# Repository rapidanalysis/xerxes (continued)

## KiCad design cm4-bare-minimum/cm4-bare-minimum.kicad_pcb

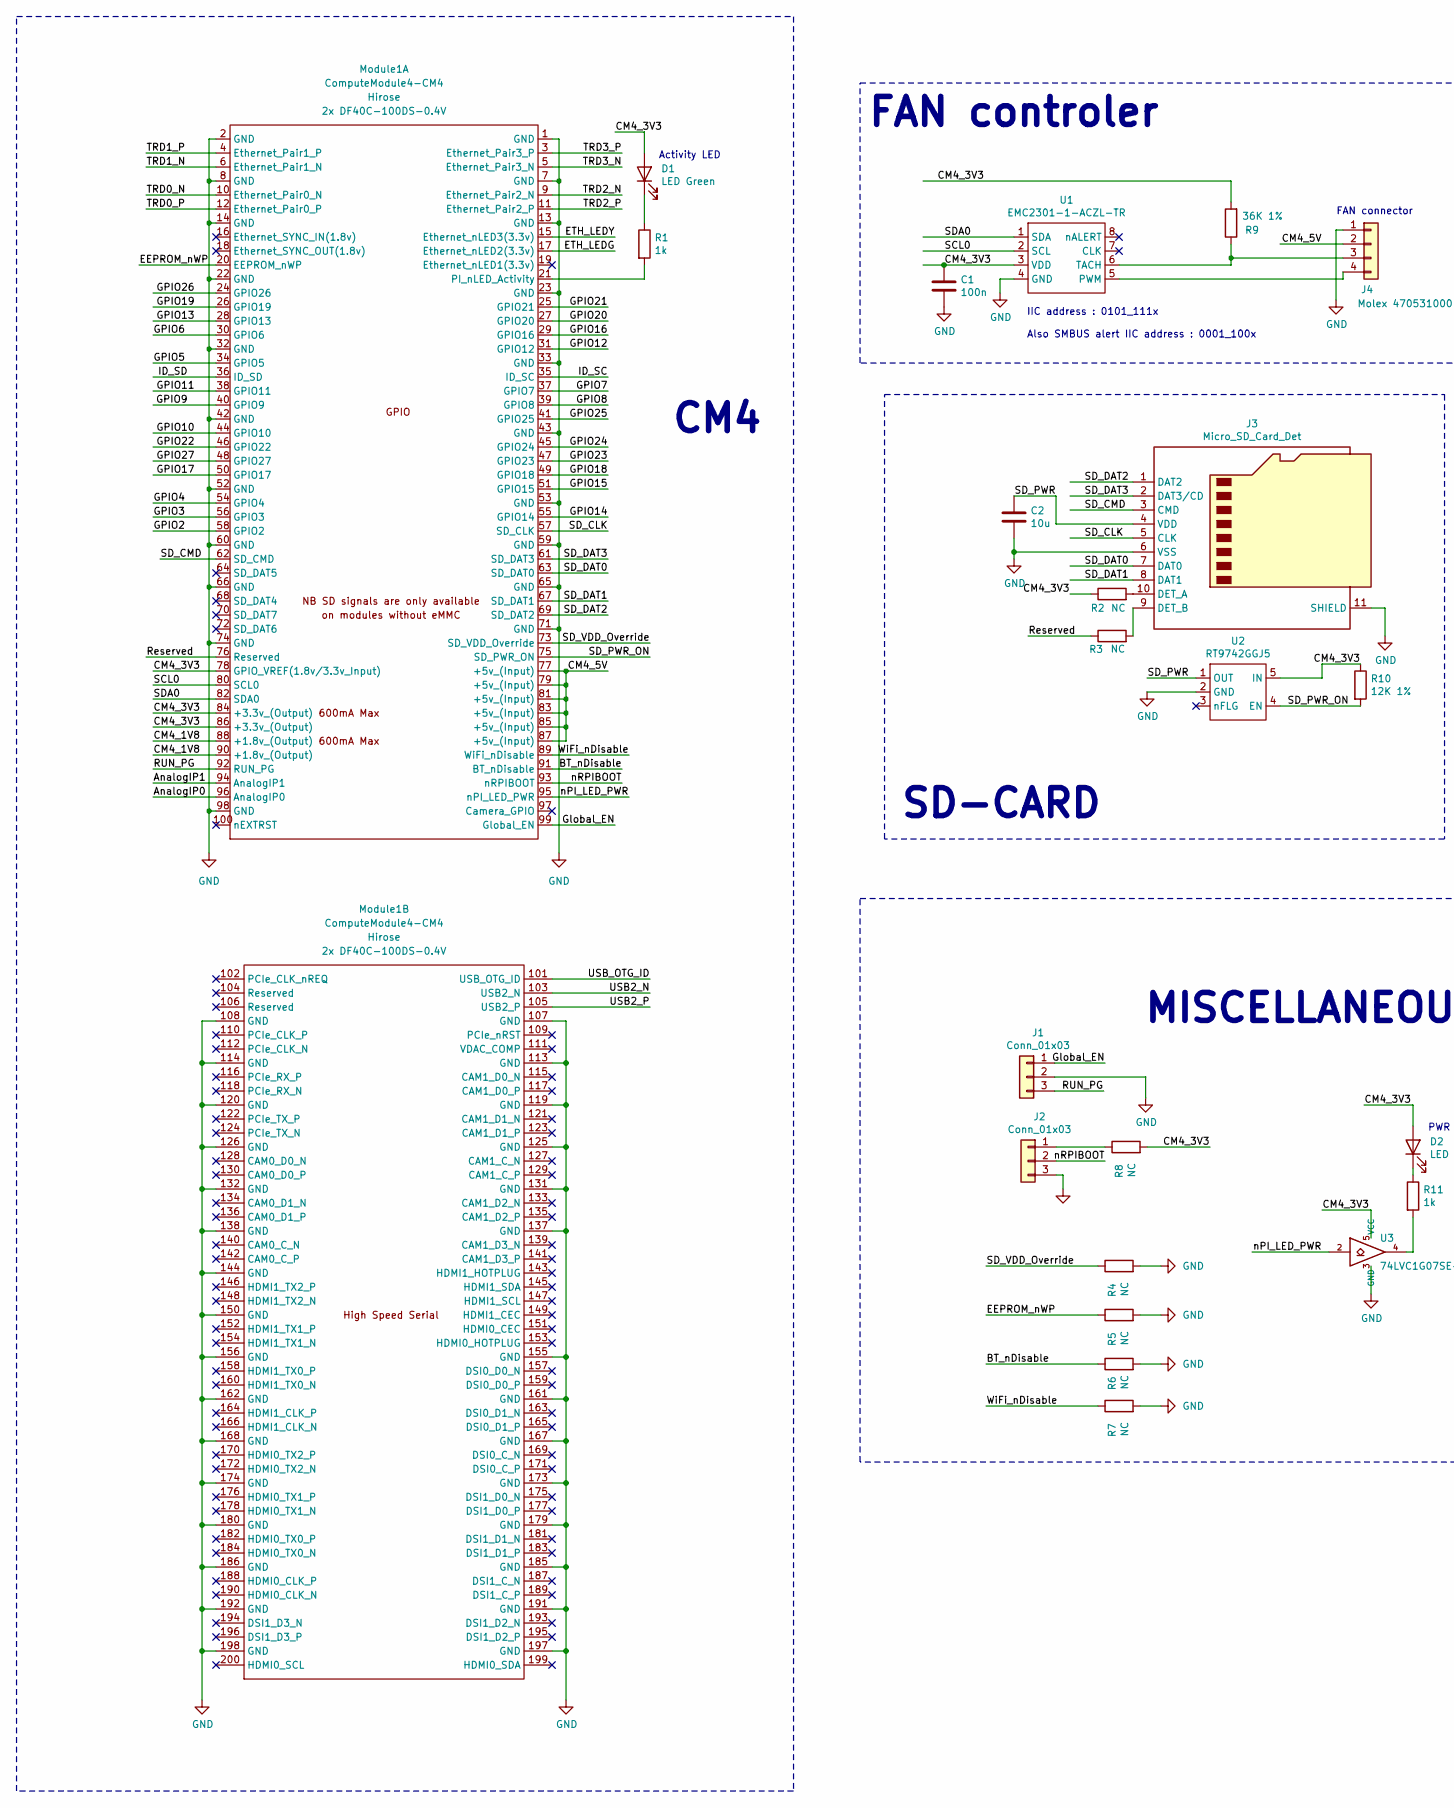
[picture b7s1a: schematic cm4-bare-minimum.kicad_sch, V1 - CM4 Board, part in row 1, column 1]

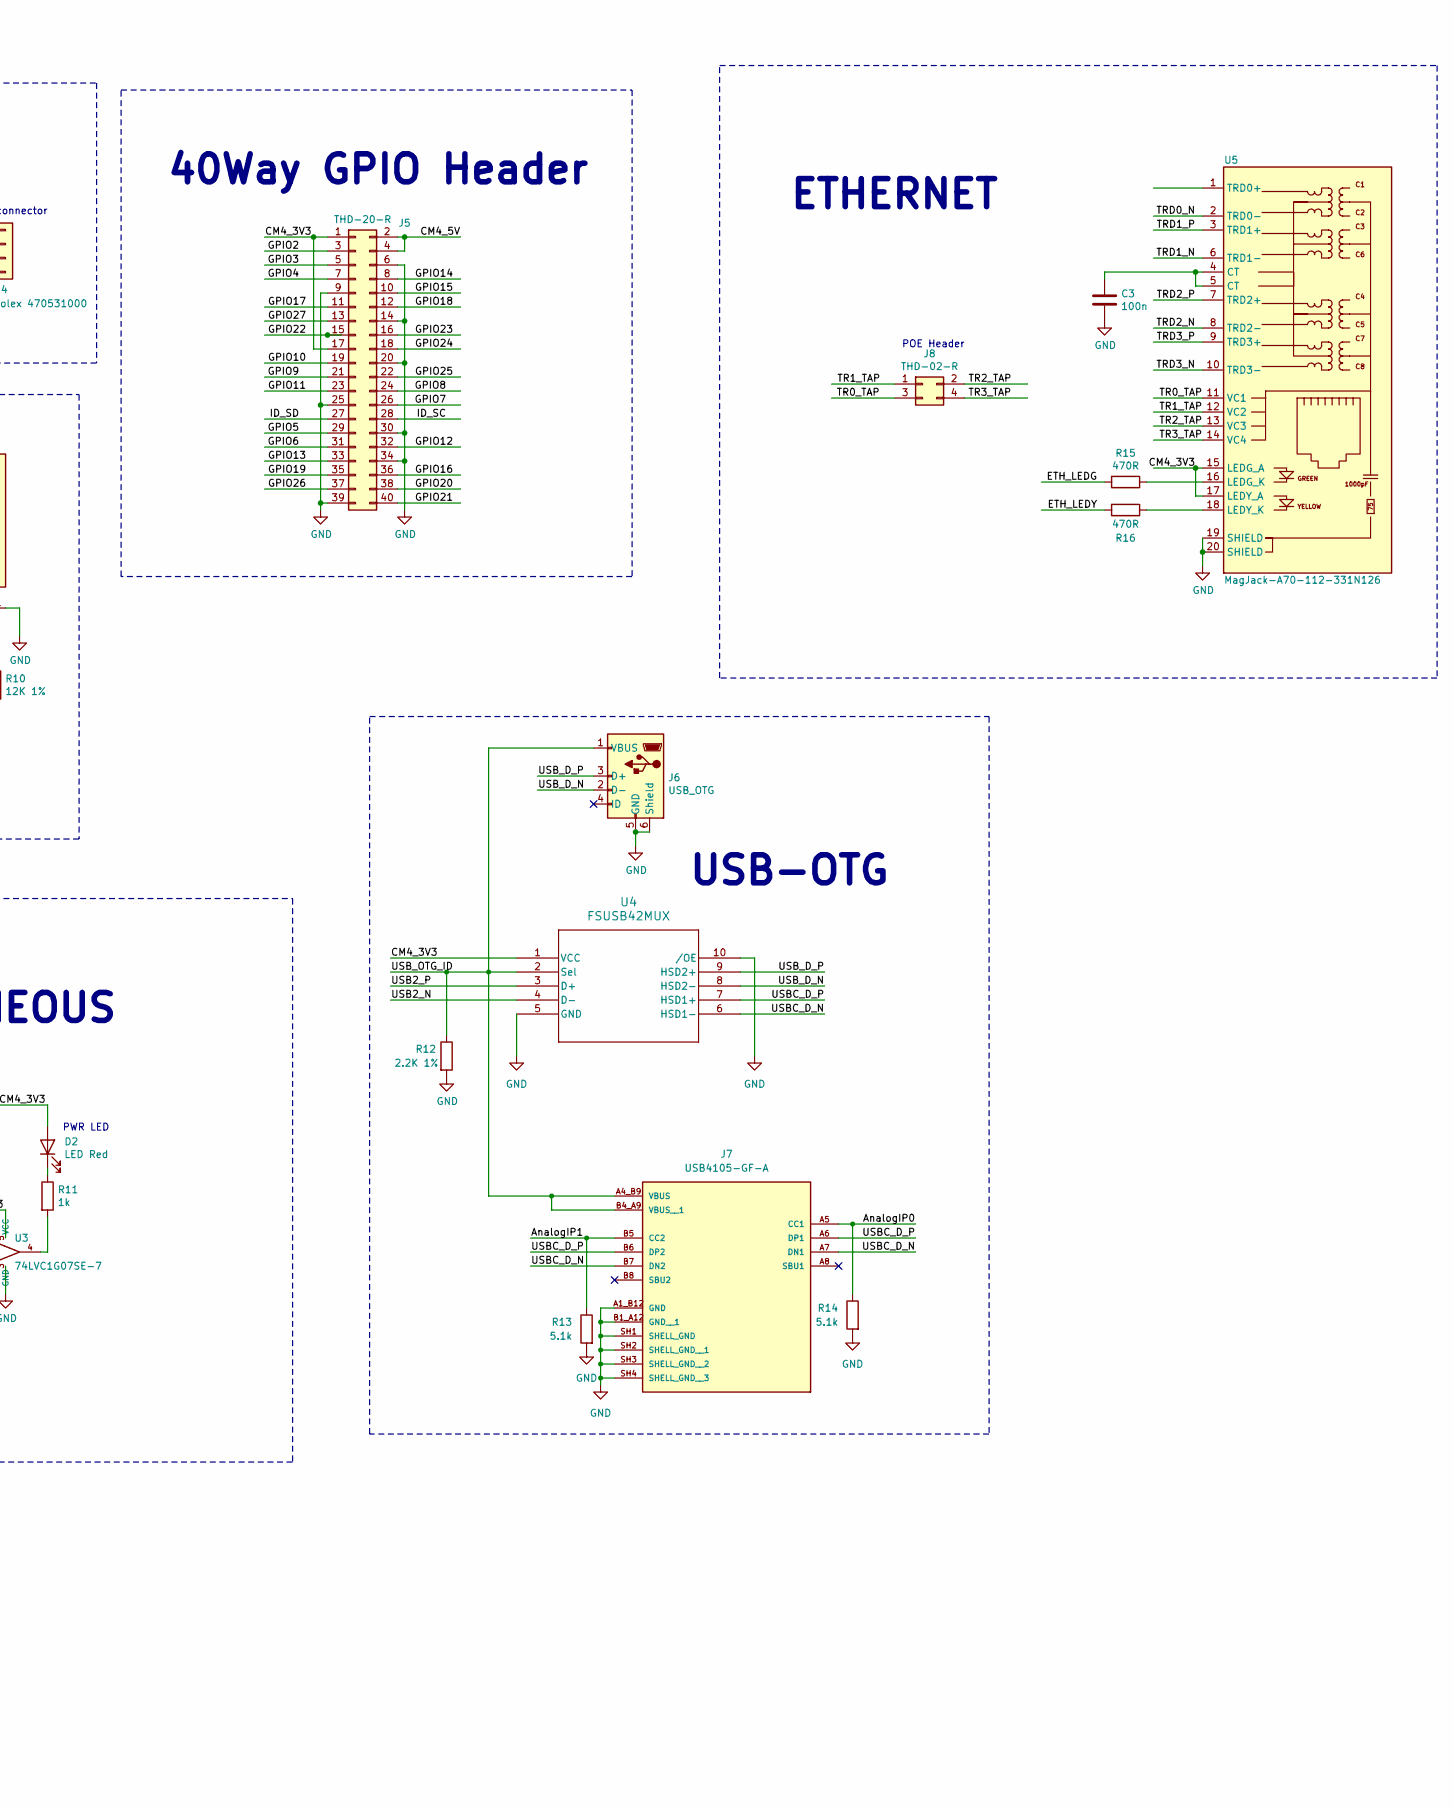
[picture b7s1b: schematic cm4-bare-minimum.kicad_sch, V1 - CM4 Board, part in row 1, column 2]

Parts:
C1, C3: 100n; C_0402_1005Metric; Part Description 0.1uF 10% 16V Ceramic Capacitor X7R 040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
C2: 10u; C_0805_2012Metric; Part Description 10uF 10% 10V Ceramic Capacitor X7R 0805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
D1: LED Green; LED_0603_1608Metric; Part Description Green 572nm LED Indication - Discrete 2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
D2: LED Red; LED_0603_1608Metric; Part Description Red 620nm LED Indication - Discrete 2.2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
J1, J2: Conn_01x03; PinHeader_1x03_P2.54mm_Vertical; Part Description 3pin 0.1" connector
J3: Micro_SD_Card_Det; SDCARD_MOLEX_503398-1892; Part Description 9 (8 + 1) Position Card Connector micro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
J4: Molex 470531000; FanPinHeader_1x04_P2.54mm_Vertical; Part Description Connector Header Through Hole 4 positio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
J5: THD-20-R; PinHeader_2x20_P2.54mm_Vertical; Part Description PinHeader_2x20_P2.54mm_Vertical
J6: USB_OTG; USB_Micro-B_EDAC_UCON00686; Part Description USB - micro B USB 2.0 Receptacle Connec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
J7: USB4105-GF-A; GCT_USB4105-GF-A; PARTREV B4
J8: THD-02-R; PinHeader_2x02_P2.54mm_Vertical; Part Description PinHeader_2x02_P2.54mm_Vertical
Module1: ComputeModule4-CM4; Raspberry-Pi-4-Compute-Module
R1, R11: 1k; R_0402_1005Metric; Part Description Resistor 1K M1005 1% 63mW
R2, R3: NC; R_0402_1005Metric; Part Description Resistor 1K M1005 1% 63mW
R4, R5, R6, R7, R8: NC; R_0402_1005Metric; Part Description Resistor 2.2K M1005 1% 63mW
R9: 36K 1%; R_0402_1005Metric; Part Description Resistor 36K M1005 1% 63mW
R10: 12K 1%; R_0402_1005Metric; Part Description Resistor 12K M1005 1% 63mW
R12: 2.2K 1%; R_0402_1005Metric; Part Description Resistor 2.2K M1005 1% 63mW
R13, R14: 5.1k; R_0402_1005Metric
R15, R16: 470R; R_0402_1005Metric; Part Description Resistor 470R M1005 1% 63mW
U1: EMC2301-1-ACZL-TR; MSOP-8_3x3mm_P0.65mm; Part Description Motor Driver PWM 8-MSOP
U2: RT9742GGJ5; SOT-23-5; Part Description Power Switch/Driver 1:1 N-Channel 1A TS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
U3: 74LVC1G07SE-7; SOT-353_SC-70-5; Part Description Buffer, Non-Inverting 1 Element 1 Bit p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
U4: FSUSB42MUX; MSOP10_3X3_ONS
U5: MagJack-A70-112-331N126; TRJG0926HENL; Part Description Gigabit Ethernet Magjack

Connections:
/AnalogIP0: J7.A5 (CC1), Module1.96 (AnalogIP0), R14.1
/AnalogIP1: J7.B5 (CC2), Module1.94 (AnalogIP1), R13.1
/BT_nDisable: Module1.91 (BT_nDisable), R6.1
/CM4_1V8: Module1.88 (+1.8v_(Output)), Module1.90 (+1.8v_(Output))
/CM4_3V3: C1.1, D1.2 (A), D2.2 (A), J5.1, J5.17, Module1.78 (GPIO_VREF(1.8v/3.3v_Input)), Module1.84 (+3.3v_(Output)), Module1.86 (+3.3v_(Output)), R2.1, R8.2, R9.2, R10.1, U1.3 (VDD), U2.5 (IN), U3.5 (VCC), U4.1 (VCC), U5.15 (LEDG_A), U5.17 (LEDY_A)
/CM4_5V: J4.2, J5.2, J5.4, Module1.77 (+5v_(Input)), Module1.79 (+5v_(Input)), Module1.81 (+5v_(Input)), Module1.83 (+5v_(Input)), Module1.85 (+5v_(Input)), Module1.87 (+5v_(Input))
/EEPROM_nWP: Module1.20 (EEPROM_nWP), R5.1
/ETH_LEDG: Module1.17 (Ethernet_nLED2(3.3v)), R15.2
/ETH_LEDY: Module1.15 (Ethernet_nLED3(3.3v)), R16.2
/GPIO2: J5.3, Module1.58 (GPIO2)
/GPIO3: J5.5, Module1.56 (GPIO3)
/GPIO4: J5.7, Module1.54 (GPIO4)
/GPIO5: J5.29, Module1.34 (GPIO5)
/GPIO6: J5.31, Module1.30 (GPIO6)
/GPIO7: J5.26, Module1.37 (GPIO7)
/GPIO8: J5.24, Module1.39 (GPIO8)
/GPIO9: J5.21, Module1.40 (GPIO9)
/GPIO10: J5.19, Module1.44 (GPIO10)
/GPIO11: J5.23, Module1.38 (GPIO11)
/GPIO12: J5.32, Module1.31 (GPIO12)
/GPIO13: J5.33, Module1.28 (GPIO13)
/GPIO14: J5.8, Module1.55 (GPIO14)
/GPIO15: J5.10, Module1.51 (GPIO15)
/GPIO16: J5.36, Module1.29 (GPIO16)
/GPIO17: J5.11, Module1.50 (GPIO17)
/GPIO18: J5.12, Module1.49 (GPIO18)
/GPIO19: J5.35, Module1.26 (GPIO19)
/GPIO20: J5.38, Module1.27 (GPIO20)
/GPIO21: J5.40, Module1.25 (GPIO21)
/GPIO22: J5.15, Module1.46 (GPIO22)
/GPIO23: J5.16, Module1.47 (GPIO23)
/GPIO24: J5.18, Module1.45 (GPIO24)
/GPIO25: J5.22, Module1.41 (GPIO25)
/GPIO26: J5.37, Module1.24 (GPIO26)
/GPIO27: J5.13, Module1.48 (GPIO27)
/Global_EN: J1.1, Module1.99 (Global_EN)
/ID_SC: J5.28, Module1.35 (ID_SC)
/ID_SD: J5.27, Module1.36 (ID_SD)
/RUN_PG: J1.3, Module1.92 (RUN_PG)
/Reserved: Module1.76 (Reserved), R3.1
/SCL0: Module1.80 (SCL0), U1.2 (SCL)
/SDA0: Module1.82 (SDA0), U1.1 (SDA)
/SD_CLK: J3.5 (CLK), Module1.57 (SD_CLK)
/SD_CMD: J3.3 (CMD), Module1.62 (SD_CMD)
/SD_DAT0: J3.7 (DAT0), Module1.63 (SD_DAT0)
/SD_DAT1: J3.8 (DAT1), Module1.67 (SD_DAT1)
/SD_DAT2: J3.1 (DAT2), Module1.69 (SD_DAT2)
/SD_DAT3: J3.2 (DAT3/CD), Module1.61 (SD_DAT3)
/SD_PWR: C2.1, J3.4 (VDD), U2.1 (OUT)
/SD_PWR_ON: Module1.75 (SD_PWR_ON), R10.2, U2.4 (EN)
/SD_VDD_Override: Module1.73 (SD_VDD_Override), R4.1
/TR0_TAP: J8.3, U5.11 (VC1)
/TR1_TAP: J8.1, U5.12 (VC2)
/TR2_TAP: J8.2, U5.13 (VC3)
/TR3_TAP: J8.4, U5.14 (VC4)
/TRD0_N: Module1.10 (Ethernet_Pair0_N), U5.2 (TRD0-)
/TRD0_P: Module1.12 (Ethernet_Pair0_P)
/TRD1_N: Module1.6 (Ethernet_Pair1_N), U5.6 (TRD1-)
/TRD1_P: Module1.4 (Ethernet_Pair1_P), U5.3 (TRD1+)
/TRD2_N: Module1.9 (Ethernet_Pair2_N), U5.8 (TRD2-)
/TRD2_P: Module1.11 (Ethernet_Pair2_P), U5.7 (TRD2+)
/TRD3_N: Module1.5 (Ethernet_Pair3_N), U5.10 (TRD3-)
/TRD3_P: Module1.3 (Ethernet_Pair3_P), U5.9 (TRD3+)
/USB2_N: Module1.103 (USB2_N), U4.4 (D-)
/USB2_P: Module1.105 (USB2_P), U4.3 (D+)
/USBC_D_N: J7.A7 (DN1), J7.B7 (DN2), U4.6 (HSD1-)
/USBC_D_P: J7.A6 (DP1), J7.B6 (DP2), U4.7 (HSD1+)
/USB_D_N: J6.2 (D-), U4.8 (HSD2-)
/USB_D_P: J6.3 (D+), U4.9 (HSD2+)
/USB_OTG_ID: J6.1 (VBUS), J7.A4_B9 (VBUS), J7.B4_A9 (VBUS__1), Module1.101 (USB_OTG_ID), R12.1, U4.2 (Sel)
/WiFi_nDisable: Module1.89 (WiFi_nDisable), R7.1
/nPI_LED_PWR: Module1.95 (nPI_LED_PWR), U3.2
/nRPIBOOT: J2.2, Module1.93 (nRPIBOOT)
GND: C1.2, C2.2, C3.2, J1.2, J2.3, J3.6 (VSS), J3.11 (SHIELD), J4.1, J5.6, J5.9, J5.14, J5.20, J5.25, J5.30, J5.34, J5.39, J6.5 (GND), J6.6 (Shield), J7.A1_B12 (GND), J7.B1_A12 (GND__1), J7.SH1 (SHELL_GND), J7.SH2 (SHELL_GND__1), J7.SH3 (SHELL_GND__2), J7.SH4 (SHELL_GND__3), Module1.1 (GND), Module1.2 (GND), Module1.7 (GND), Module1.8 (GND), Module1.13 (GND), Module1.14 (GND), Module1.22 (GND), Module1.23 (GND), Module1.32 (GND), Module1.33 (GND), Module1.42 (GND), Module1.43 (GND), Module1.52 (GND), Module1.53 (GND), Module1.59 (GND), Module1.60 (GND), Module1.65 (GND), Module1.66 (GND), Module1.71 (GND), Module1.74 (GND), Module1.98 (GND), Module1.107 (GND), Module1.108 (GND), Module1.113 (GND), Module1.114 (GND), Module1.119 (GND), Module1.120 (GND), Module1.125 (GND), Module1.126 (GND), Module1.131 (GND), Module1.132 (GND), Module1.137 (GND), Module1.138 (GND), Module1.144 (GND), Module1.150 (GND), Module1.155 (GND), Module1.156 (GND), Module1.161 (GND), Module1.162 (GND), Module1.167 (GND), Module1.168 (GND), Module1.173 (GND), Module1.174 (GND), Module1.179 (GND), Module1.180 (GND), Module1.185 (GND), Module1.186 (GND), Module1.191 (GND), Module1.192 (GND), Module1.197 (GND), Module1.198 (GND), R4.2, R5.2, R6.2, R7.2, R12.2, R13.2, R14.2, U1.4 (GND), U2.2 (GND), U3.3 (GND), U4.5 (GND), U4.10 (/OE), U5.19 (SHIELD), U5.20 (SHIELD)
unnamed: C3.1, U5.4 (CT), U5.5 (CT)
unnamed: D1.1 (K), R1.1
unnamed: D2.1 (K), R11.1
unnamed: J2.1, R8.1
unnamed: J3.10 (DET_A), R2.2
unnamed: J3.9 (DET_B), R3.2
unnamed: J4.3, R9.1, U1.6 (TACH)
unnamed: J4.4, U1.5 (PWM)
unnamed: Module1.21 (PI_nLED_Activity), R1.2
unnamed: R11.2, U3.4
unnamed: R15.1, U5.16 (LEDG_K)
unnamed: R16.1, U5.18 (LEDY_K)

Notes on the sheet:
FAN controler
40Way GPIO Header
IIC address : 0101_111x
FAN connector
PWR LED
Activity LED
POE Header
Also SMBUS alert IIC address : 0001_100x
MISCELLANEOUS
USB-OTG
ETHERNET
CM4
SD-CARD

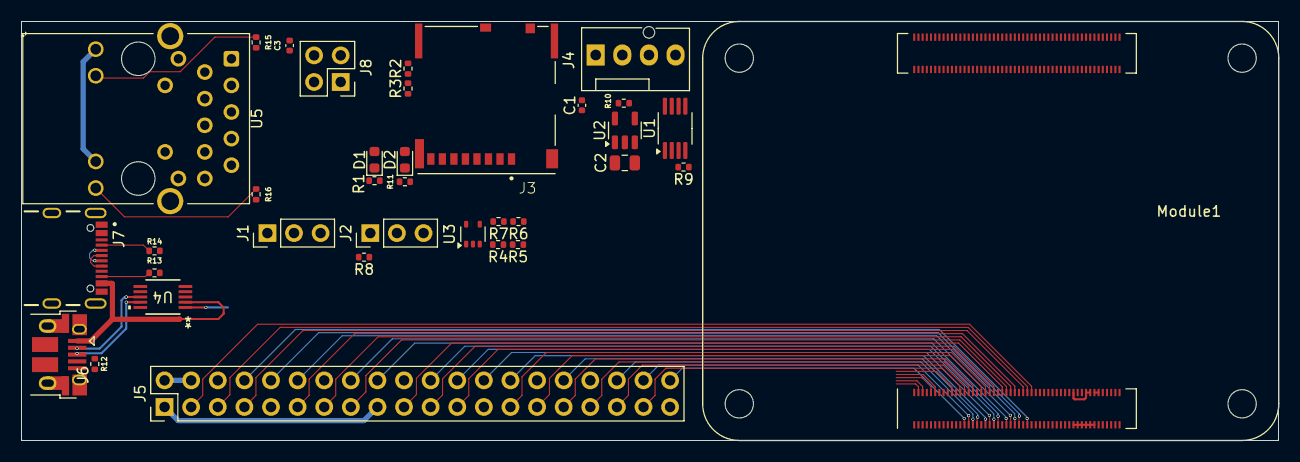
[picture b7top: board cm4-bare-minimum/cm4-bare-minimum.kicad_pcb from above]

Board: 2 copper layers, 120.0 x 40.0 mm, 35 parts (0 on the bottom side), 85 nets.

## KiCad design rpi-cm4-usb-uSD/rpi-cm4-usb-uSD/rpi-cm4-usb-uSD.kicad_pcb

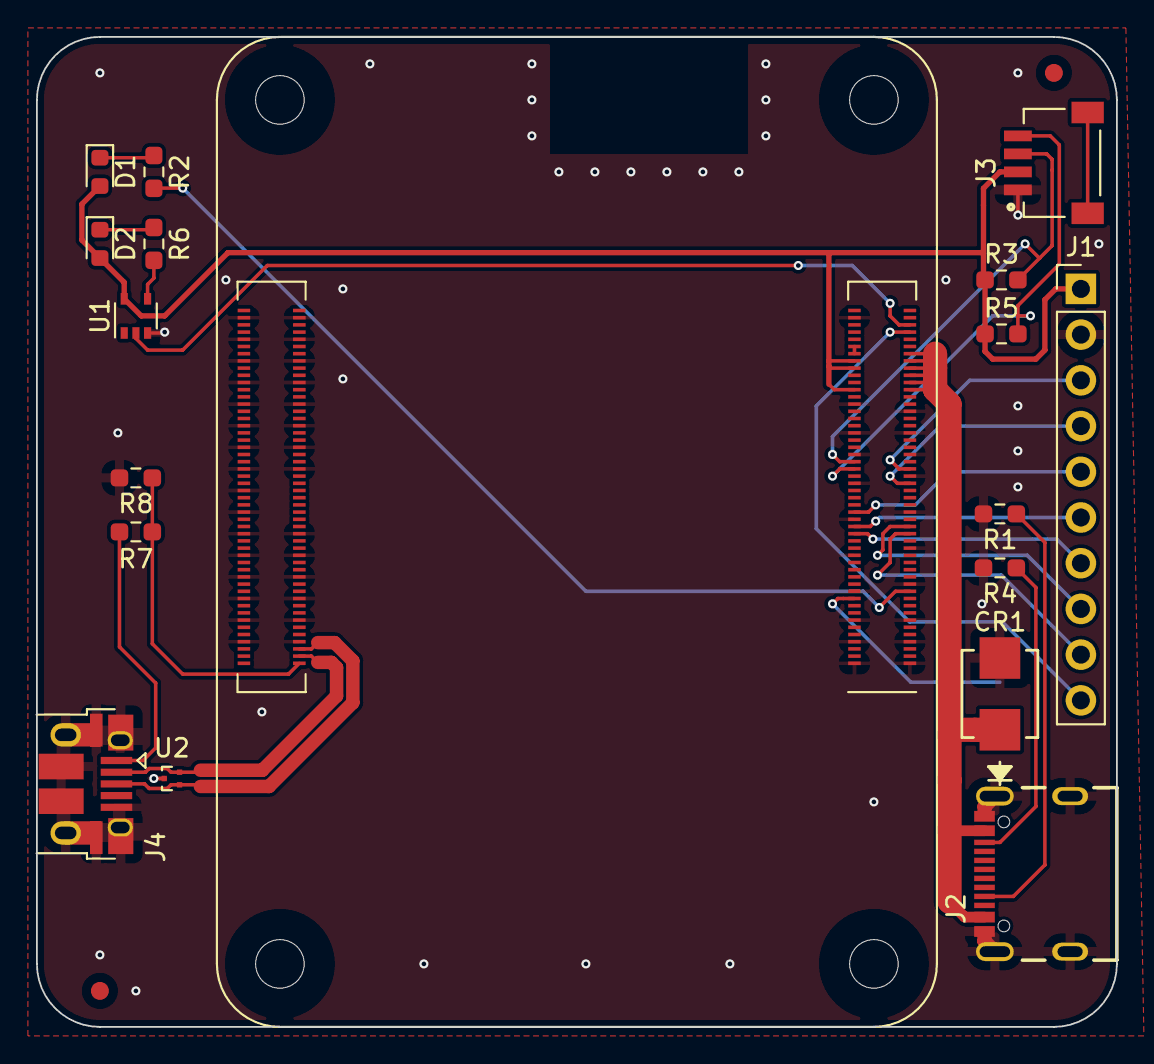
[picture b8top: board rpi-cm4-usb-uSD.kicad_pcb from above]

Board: 2 copper layers, 60.0 x 55.0 mm, 19 parts (1 on the bottom side), 27 nets.

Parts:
CR1: SMBJ5.0A-TR
D1: LED Green; LED_0603_1608Metric
D2: LED Red; LED_0603_1608Metric
J1: DNP; PinHeader_1x10_P2.54mm_Vertical
J2: USB4105-GF-A; GCT_USB4105-GF-A
J3: SM04B-SRSS-TB(LF)(SN); JST_SM04B-SRSS-TB(LF)(SN)
J4: USB_OTG; USB_Micro-B_EDAC_UCON00686
JP1: SolderJumper_2_Open; SolderJumper-2_P1.3mm_Open_RoundedPad1.0x1.5mm
Module1: ComputeModule4-CM4; Raspberry-Pi-4-Compute-Module
R1, R4: 5.1k; R_0603_1608Metric_Pad0.98x0.95mm_HandSolder
R2, R6: 1k; R_0603_1608Metric_Pad0.98x0.95mm_HandSolder
R3, R5: DNP; R_0603_1608Metric_Pad0.98x0.95mm_HandSolder
R7, R8: 2.2K 1%; R_0603_1608Metric_Pad0.98x0.95mm_HandSolder
U1: 74LVC1G07SE-7; SOT-353_SC-70-5
U2: TPD2EUSB30; Texas_DRT-3

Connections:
+1.8V: Module1.88 (+1.8v_(Output)), Module1.90 (+1.8v_(Output))
+3.3V: D1.2 (A), D2.2 (A), J1.1, J3.2, Module1.78 (GPIO_VREF(1.8v/3.3v_Input)), Module1.84 (+3.3v_(Output)), Module1.86 (+3.3v_(Output)), R3.1, R5.1, U1.5 (VCC)
+5V: CR1.1, J2.A4/B9 (VBUS), J2.B4/A9 (VBUS), Module1.77 (+5v_(Input)), Module1.79 (+5v_(Input)), Module1.81 (+5v_(Input)), Module1.83 (+5v_(Input)), Module1.85 (+5v_(Input)), Module1.87 (+5v_(Input))
/CM4 GPIO/EEPROM_nWP: JP1.1 (A), Module1.20 (EEPROM_nWP)
/CM4 GPIO/GPIO2: J3.3, Module1.58 (GPIO2), R3.2
/CM4 GPIO/GPIO3: J3.4, Module1.56 (GPIO3), R5.2
/CM4 GPIO/GPIO7: J1.9, Module1.37 (GPIO7)
/CM4 GPIO/GPIO8: J1.8, Module1.39 (GPIO8)
/CM4 GPIO/GPIO9: J1.6, Module1.40 (GPIO9)
/CM4 GPIO/GPIO10: J1.5, Module1.44 (GPIO10)
/CM4 GPIO/GPIO11: J1.7, Module1.38 (GPIO11)
/CM4 GPIO/GPIO14: J1.3, Module1.55 (GPIO14)
/CM4 GPIO/GPIO15: J1.4, Module1.51 (GPIO15)
/CM4 GPIO/nLED_Activity: Module1.21 (PI_nLED_Activity), R2.2
/CM4 GPIO/nPWR_LED: Module1.95 (nPI_LED_PWR), U1.2
/CM4 GPIO/nRPIBOOT: J1.10, Module1.93 (nRPIBOOT)
/CM4 High Speed/USB2_N: J4.2 (D-), Module1.103 (USB2_N), U2.2 (D-)
/CM4 High Speed/USB2_P: J4.3 (D+), Module1.105 (USB2_P), U2.1 (D+)
/CM4 High Speed/USB_OTG_ID: Module1.101 (USB_OTG_ID), R7.2, R8.1
GND: CR1.2, J1.2, J2.A1/B12 (GND), J2.B1/A12 (GND), J2.G1 (GND), J2.G2 (GND), J2.G3 (GND), J2.G4 (GND), J3.1, J4.5 (GND), J4.6 (Shield), JP1.2 (B), Module1.1 (GND), Module1.2 (GND), Module1.7 (GND), Module1.8 (GND), Module1.13 (GND), Module1.14 (GND), Module1.22 (GND), Module1.23 (GND), Module1.32 (GND), Module1.33 (GND), Module1.42 (GND), Module1.43 (GND), Module1.52 (GND), Module1.53 (GND), Module1.59 (GND), Module1.60 (GND), Module1.65 (GND), Module1.66 (GND), Module1.71 (GND), Module1.74 (GND), Module1.98 (GND), Module1.107 (GND), Module1.108 (GND), Module1.113 (GND), Module1.114 (GND), Module1.119 (GND), Module1.120 (GND), Module1.125 (GND), Module1.126 (GND), Module1.131 (GND), Module1.132 (GND), Module1.137 (GND), Module1.138 (GND), Module1.144 (GND), Module1.150 (GND), Module1.155 (GND), Module1.156 (GND), Module1.161 (GND), Module1.162 (GND), Module1.167 (GND), Module1.168 (GND), Module1.173 (GND), Module1.174 (GND), Module1.179 (GND), Module1.180 (GND), Module1.185 (GND), Module1.186 (GND), Module1.191 (GND), Module1.192 (GND), Module1.197 (GND), Module1.198 (GND), R1.2, R4.2, R8.2, U1.3 (GND), U2.3 (GND)
unnamed: D1.1 (K), R2.1
unnamed: D2.1 (K), R6.1
unnamed: J2.A5 (CC1), R1.1
unnamed: J2.B5 (CC2), R4.1
unnamed: J3.S1 (SHIELD), J3.S2 (SHIELD)
unnamed: J4.1 (VBUS), R7.1
unnamed: R6.2, U1.4

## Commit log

2024-10-25 RPI CM4 Board Template Project
    Contains all bare minimum requirements for the CM4 board. HDMI, USB, SD-Card, OTG power, Ethernet. Clone this repository and make your changes to the template project schematics as required.
2024-10-25 Added Footprint Files
2024-10-25 Modified gitignore
2024-10-25 Updated hierarchy
2024-10-25 Added README Again
2024-10-27 PCB Layout Updated
    Shows how much room we have to work with on the PCB.
2024-10-31 Added CSI connector and associated library
2024-11-01 Added New Bare Minimum Project
    Single Sheet Schematic, simplified view, shows only the required modules.
    PCB layout needs to be adjusted and tracks need to be drawn.
    Libraries are in a single directory for ease.
2024-11-02 Added uSD and support for 2 USB3 schematic
2024-11-03 Connector changed, Added Labels.
    Changed HDMI connector to upright. Added labels for included components in schematic.
    To Do: Create tracks in PCB Layout. Add jumper for wifi bluetooth signals.
2024-11-08 updated V1 bare minimum board
    Initiated pcb layout for V1 board
2024-11-09 Renamed V1 Requirements project
2024-11-10 PCB Layout Modified to Nano-ITX
    Added M.2 connector, PSU, updated PCB layout for 120mm x 120mm. Connected GPIO header. Working on remaining component and tracks placement.
2024-11-10 Updated V1 PCB Layout
    Added Mounting Holes
2024-11-14 Housekeeping, board size 120mmx40mm
    V1 requirements are fulfilled, Connections are remaining in PCB layout, Performed Cleanup of repo so it only has the V1 Project.
2024-11-14 Fixed Typo in Schematic
2024-11-15 Updated PCB layout
2024-11-23 Completed V1, Generated Output Files
    Finished PCB layout, fixed all design rule violations and completed the design. Gerber files, Drill files, Bill of Materials, generated.
2024-11-23 Update Drill Report
2024-11-23 Reorganization of Output Files
    Added each Fabrication Output file in its own directory for ease of viewing. Also included schematic drawing in Output.
2024-11-24 Added PCBWay Order Files
2024-11-24 Update README
    Added Feature Details to README, included images for better viewing.
2024-12-17 M.2 and CSI integration
    Changed from CM4 to CM5 rails, included M.2 and CSI connectors, added "Rapid Analysis" to silkscreen. Added some thermal management layers. Streamlined the schematic (hierarchical representation)
2024-12-17 Minor corrections to Blade Design
2024-12-17 Sent for production to PCBWay.
2025-01-14 Added 3D Render
    Added 3D images and high quality images with RayTracing enabled.
2025-01-16 Fixing Blade Carrier Board
2025-01-22 Started Blade V2 project
    Attempt to fix some of the issues with the Blade V1 board. Reverting from CM5 back to CM4. Changing some alignment issues.
2025-01-25 Blade_v2 Final revision
2025-03-04 Blade_V3 Commit
2025-03-16 Latest Version Commit
2025-03-26 Added POE Daughter Card
    POE Daughter card for attaching AG5405
2025-12-12 Xerxes-Pi (Rev 2) INIT
